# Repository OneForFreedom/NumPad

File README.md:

# NumPad
A full numpad with all 17 keys, basically the opposite of a ten keyless keyboard

## Eye Candy!!

## BOM (Bill of Materials)

| BOM Name     | Quantity | Link | US Price | UK Price |
| ------------ | -------- | ---- | -------- | -------- |
| switches     | 17       |      |          |          |
| diode        | 17       |      |          |          |
| XIAO-RP2040  | 1        |      |          |          |
| keycap-white | 14       |      |          |          |
| Stabilizer   | 1        | [AliExpress](https://www.aliexpress.com/item/32890298703.html) |   16.78       |   12.39        |
| 2u Keycap    | 3       |  [AliExpress](https://www.aliexpress.com/item/1005008632794638.html)    |  4.13    |   3.06   |

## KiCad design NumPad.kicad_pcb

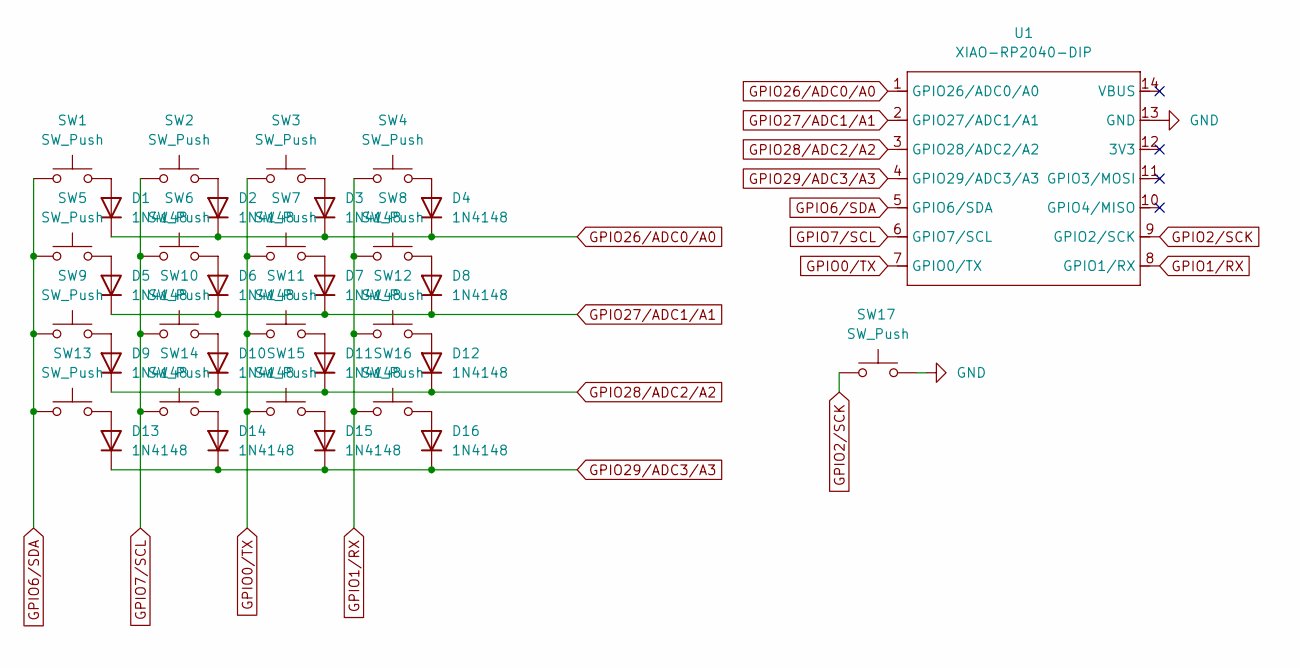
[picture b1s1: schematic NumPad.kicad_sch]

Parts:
D1, D2, D3, D4, D5, D6, D7, D8, D9, D10, D11, D12, D13, D14, D15, D16: 1N4148; D_DO-35_SOD27_P7.62mm_Horizontal
SW1, SW2, SW3, SW4, SW5, SW6, SW7, SW9, SW10, SW11, SW12, SW13, SW14, SW17: SW_Push; SW_Cherry_MX_1.00u_PCB WITH 3D
SW8, SW15, SW16: SW_Push; SW_Cherry_MX_2.00u_PCB
U1: XIAO-RP2040-DIP

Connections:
GND: SW17.2, U1.13 (GND)
GPIO0/TX: SW3.1, SW7.1, SW11.1, SW15.1, U1.7 (GPIO0/TX)
GPIO1/RX: SW4.1, SW8.1, SW12.1, SW16.1, U1.8 (GPIO1/RX)
GPIO2/SCK: SW17.1, U1.9 (GPIO2/SCK)
GPIO6/SDA: SW1.1, SW5.1, SW9.1, SW13.1, U1.5 (GPIO6/SDA)
GPIO7/SCL: SW2.1, SW6.1, SW10.1, SW14.1, U1.6 (GPIO7/SCL)
GPIO26/ADC0/A0: D1.1 (K), D2.1 (K), D3.1 (K), D4.1 (K), U1.1 (GPIO26/ADC0/A0)
GPIO27/ADC1/A1: D5.1 (K), D6.1 (K), D7.1 (K), D8.1 (K), U1.2 (GPIO27/ADC1/A1)
GPIO28/ADC2/A2: D9.1 (K), D10.1 (K), D11.1 (K), D12.1 (K), U1.3 (GPIO28/ADC2/A2)
GPIO29/ADC3/A3: D13.1 (K), D14.1 (K), D15.1 (K), D16.1 (K), U1.4 (GPIO29/ADC3/A3)
unnamed: D1.2 (A), SW1.2
unnamed: D2.2 (A), SW2.2
unnamed: D3.2 (A), SW3.2
unnamed: D4.2 (A), SW4.2
unnamed: D5.2 (A), SW5.2
unnamed: D6.2 (A), SW6.2
unnamed: D7.2 (A), SW7.2
unnamed: D8.2 (A), SW8.2
unnamed: D9.2 (A), SW9.2
unnamed: D10.2 (A), SW10.2
unnamed: D11.2 (A), SW11.2
unnamed: D12.2 (A), SW12.2
unnamed: D13.2 (A), SW13.2
unnamed: D14.2 (A), SW14.2
unnamed: D15.2 (A), SW15.2
unnamed: D16.2 (A), SW16.2

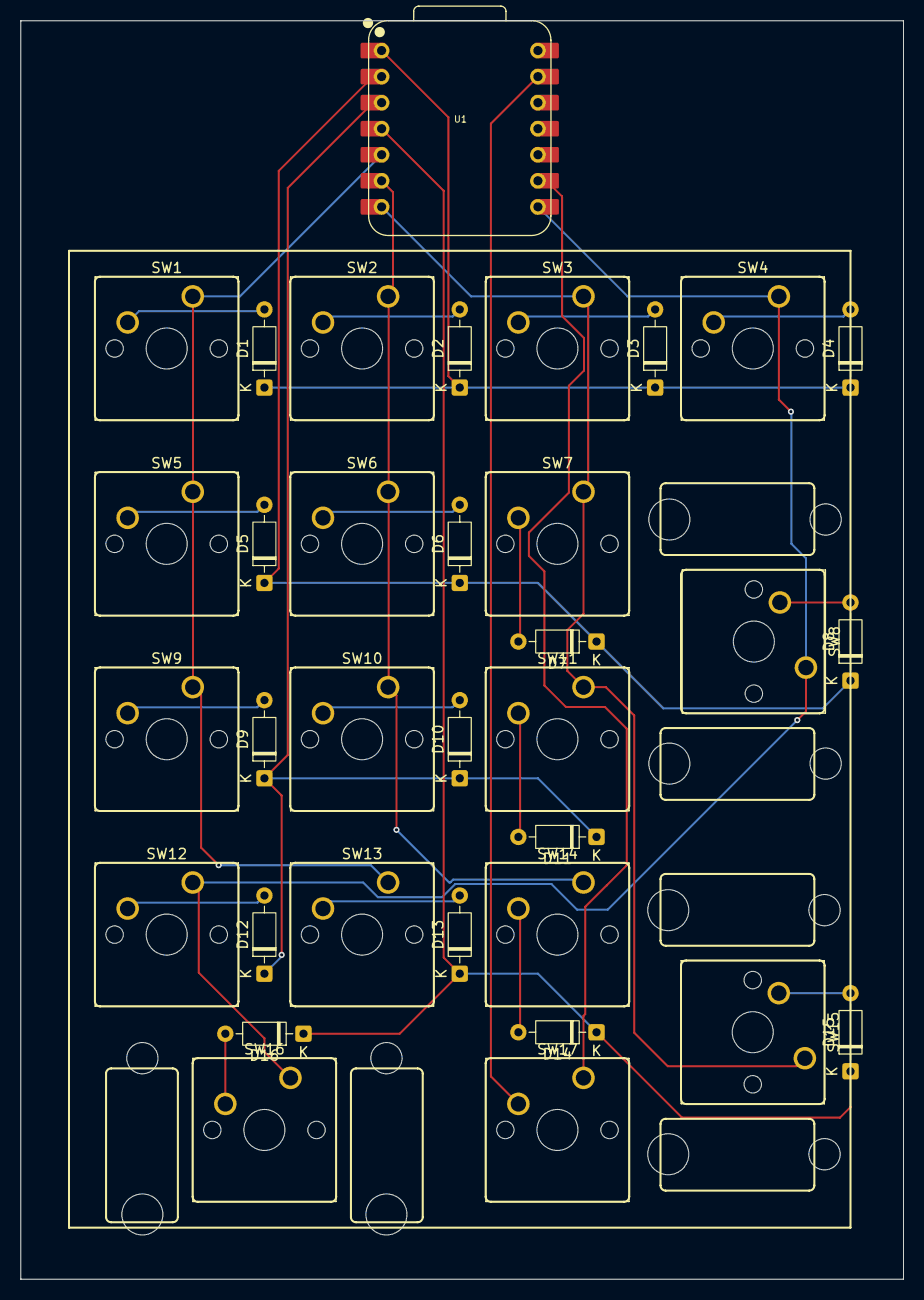
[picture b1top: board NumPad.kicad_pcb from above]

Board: 2 copper layers, 86.1 x 122.7 mm, 34 parts (0 on the bottom side), 26 nets.

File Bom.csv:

Designator,Footprint,Quantity,Value,LCSC Part #
"D1, D10, D11, D12, D13, D14, D15, D16, D2, D3, D4, D5, D6, D7, D8, D9",D_DO-35_SOD27_P7.62mm_Horizontal,16,1N4148,
"SW1, SW10, SW11, SW12, SW13, SW14, SW17, SW2, SW3, SW4, SW5, SW6, SW7, SW9",SW_Cherry_MX_1.00u_PCB WITH 3D,14,SW_Push,
"SW15, SW16, SW8",SW_Cherry_MX_2.00u_PCB,3,SW_Push,
U1,XIAO-RP2040-DIP,1,XIAO-RP2040-DIP,

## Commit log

2025-08-31 Rename NumPad.zip to Production/NumPad.zip
2025-08-31 Rename Screenshot 2025-08-31 003703.png to Images/Screenshot 2025-08-31 003703.png
